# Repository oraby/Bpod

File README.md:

# Bpod

Kepecs Lab workspace, forked from Sanworks.

Used to modify Bpod code for use in Kepecs Lab.
General improvements will be contributed to Sanworks' repo.

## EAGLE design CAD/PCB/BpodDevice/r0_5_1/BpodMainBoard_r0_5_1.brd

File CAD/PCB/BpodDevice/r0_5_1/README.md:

# Bpod r0.5.1 PCB
Minor improvements compared to the original Bpod r0.5 release:
* Added bypass-capacitors to the VCC-inputs of all ICs
* Added GND polygon on top and bottom layer
* Rerouted the layout to reduce cross-talk between adjacent output ports

## Assembly instructions
Will be updted soon...  
For now see:  
https://sites.google.com/site/bpoddocumentation/assembling-bpod/instructions

## Bill of materials (BOM)
| Part Name | Description | Manufacturer | Name | Vendor | Part-Number |
| --- | --- | --- | --- | --- | --- |
| | Arduino Due | Arduino | Arduino Due | DigiKey | [1050-1049-ND](https://www.digikey.com/product-detail/en/arduino/A000062/1050-1049-ND "DigiKey 1050-1049-ND") |
| | DC/DC Converter | TDK Lambda | CC10-0512SF-E | DigiKey | [445-2433-ND](https://www.digikey.com/product-detail/en/CC10-0512SF-E/445-2433-ND "DigiKey 445-2433-ND") |
| `VALVE_REGISTER` | Power Shift Register | Texas Instruments | TPIC6A595 | DigiKey | [296-9007-5-ND](https://www.digikey.com/product-detail/en/texas-instruments/TPIC6A595NE/296-9007-5-ND "DigiKey 296-9007-5-ND") |
| `SYNC_REGISTER` | Shift Register | Texas Instruments, STMicro, NXP, … | 74HC595 | DigiKey | [296-1600-5-ND](https://www.digikey.com/product-detail/en/texas-instruments/SN74HC595N/296-1600-5-ND "DigiKey 296-1600-5-ND") |
| `5V_3V3_1/2/3` | 5V to 3.3V Converter (noninverting hex buffer) | Texas Instruments | CD4050BE | DigiKey | [296-2056-5-ND](https://www.digikey.com/product-detail/en/texas-instruments/CD4050BE/296-2056-5-ND "DigiKey 296-2056-5-ND") |
| `OPTOCOUPLER` | Opto-Coupler | Broadcom, Avago | HCPL-2231 | DigiKey | [516-1582-5-ND ](https://www.digikey.com/product-detail/en/broadcom-limited/HCPL-2231-000E/516-1582-5-ND "DigiKey 516-1582-5-ND ") |
| `Q3, Q4` | N-Channel MOSFET | ON Semi, STMicro, Microchip, NXP,… | 2N7000 | DigiKey | [2N7000FS-ND](https://www.digikey.com/product-detail/en/on-semiconductor/2N7000/2N7000FS-ND "DigiKey 2N7000FS-ND") |
| `LED` | RGB LED | Bivar Inc. | R50RGB-F-0160 | DigiKey | [492-1179-ND](https://www.digikey.com/product-detail/en/bivar-inc/R50RGB-F-0160/492-1179-ND "DigiKey 492-1179-ND") |
| `C1, C2, C3, C4, C5, C6` | 100 nF Bypass Capacitor (Ceramic) | Vishay, Kemet, AVX, … | 100 nF, 50 V, X7R | DigiKey | [BC5137-ND](https://www.digikey.com/product-detail/en/K104K10X7RF53L2/BC5137-ND "DigiKey BC5137-ND") |
| `R1` | 47 Ohm Current Limiting Common Cathode RGB LED | Stackpole, Yageo, Vishay, TE, … | 47 Ohm, 1/4 W, 1% | DigiKey | [BC4379CT-ND](https://www.digikey.com/product-detail/en/SFR2500004709FR500/BC4379CT-ND "DigiKey BC4379CT-ND") |
| `R2, R3` | 1 kOhm Current Limiting for Opto-Coupler | Stackpole, Yageo, Vishay, TE, … | 1 kOhm, 1/4 W, 1% | DigiKey | [RNF14FTD1K00CT-ND](https://www.digikey.com/product-detail/en/RNF14FTD1K00/RNF14FTD1K00CT-ND "DigiKey [RNF14FTD1K00CT-ND") |
| `R4, R5` | 10 kOhm Pull-Up BNC-Output | Stackpole, Yageo, Vishay, TE, … | 10 kOhm, 1/4 W, 1% | DigiKey | [RNF14FTD10K0CT-ND](https://www.digikey.com/product-detail/en/RNF14FTD10K0/RNF14FTD10K0CT-ND "DigiKey RNF14FTD10K0CT-ND") |
| | Socket DIP8 (OPTOCOUPLER) | On Shore, Assmann, TE, Amphenol, ... | DIP Socket 8 Pos | DigiKey | [ED3044-5-ND](https://www.digikey.com/product-detail/en/ED08DT/ED3044-5-ND "DigiKey ED3044-5-ND") |
| | Socket DIP16 (CD4050/74HC595) | On Shore, Assmann, TE, Amphenol, ... | DIP Socket 16 Pos | DigiKey | [ED3046-5-ND](https://www.digikey.com/product-detail/en/ED16DT/ED3046-5-ND "DigiKey ED3046-5-ND") |
| | Socket DIP20 (TPIC6A595) | On Shore, Assmann, TE, Amphenol, ... | DIP Socket 20 Pos | DigiKey | [ED3054-5-ND](https://www.digikey.com/product-detail/en/ED20DT/ED3054-5-ND "DigiKey ED3054-5-ND") |
| | Pinheader for Arduino Pins 0-21 & Analog (8-Pin) | Sparkfun | Stackable Header 8 Pin | Sparkfun | [PRT-09279](https://www.sparkfun.com/products/9279 "Sparkfun PRT-09279") |
| | Pinheader for Arduino Power Pins (6-Pin) | Sparkfun | Stackable Header 6 Pin | Sparkfun | [PRT-09280](https://www.sparkfun.com/products/9280 "Sparkfun PRT-09280") |
| | Pinheader for Arduino Pins 22-53 | Sullins, Amphenol, TE, … | Pinheader 36 Pos 0.1 spacing | DigiKey | [S2011EC-18-ND](https://www.digikey.com/product-detail/en/PRPC018DAAN-RC/S2011EC-18-ND "DigiKey S2011EC-18-ND") |
| | Header for Arduino ISP Pins| Sullins, Samtec, TE, … | Header (Female) 6 Pin | DigiKey | [S7106-ND](https://www.digikey.com/product-detail/en/sullins-connector-solutions/PPPC032LFBN-RC/S7106-ND "DigiKey S7106-ND") |
| `Ports` | RJ45 Ports | TE | Modular Jack 8P8C RJ45 | DigiKey | [A31442-ND](https://www.digikey.com/product-detail/en/5555164-1/A31442-ND "DigiKey A31442-ND") |
| `BNC` | BNC Ports | TE | BNC Jack 75 Ohm | DigiKey | [A97562-ND](https://www.digikey.com/product-detail/en/1-1634622-0/A97562-ND "DigiKey A97562-ND") |
| `Spring Terminal` | Spring Terminal for Wire I/Os | TE | Terminal Block 1-1986711-0 | DigiKey | [A104562-ND](https://www.digikey.com/product-detail/en/1-1986711-0/A104562-ND "DigiKey A104562-ND") |
| | Spacer for Arduino Due | Bivar Inc.  | Round Spacer Nylon 1/4" | DigiKey | [492-1074-ND](https://www.digikey.com/product-detail/en/9908-250/492-1074-ND "DigiKey 492-1074-ND") |
| | Spacer for Bpod PCB | Bivar Inc.  | Round Spacer Nylon 3/4" | DigiKey | [492-1081-ND](https://www.digikey.com/product-detail/en/9908-750/492-1081-ND "DigiKey 492-1081-ND") |
| | Screw for Arduino Due | B&F | Screw 4-40 Phillips, 0.625" thread length | DigiKey | [H348-ND](https://www.digikey.com/product-detail/en/b-f-fastener-supply/PMS-440-0063-PH/H348-ND "H348-ND") |
| | Screw for Bpod PCB | McMaster-Carr | Screw 4-40 Phillips, 1.125" thread length | McMaster-Carr | [91772A118](https://www.mcmaster.com/91772A118 "DigiKey 91772A118") |
| | Screws for Enclosure | B&F | Screw 4-40 Phillips, 0.5" thread length | DigiKey | [H346-ND](https://www.digikey.com/product-detail/en/b-f-fastener-supply/PMS-440-0050-PH/H346-ND "DigiKey H346-ND") |
| | Hex-Nuts| McMaster-Carr | Hex Nut 1/4" 4-40 | McMaster-Carr| [90480A005](https://www.mcmaster.com/90480A005 "DigiKey 90480A005") |

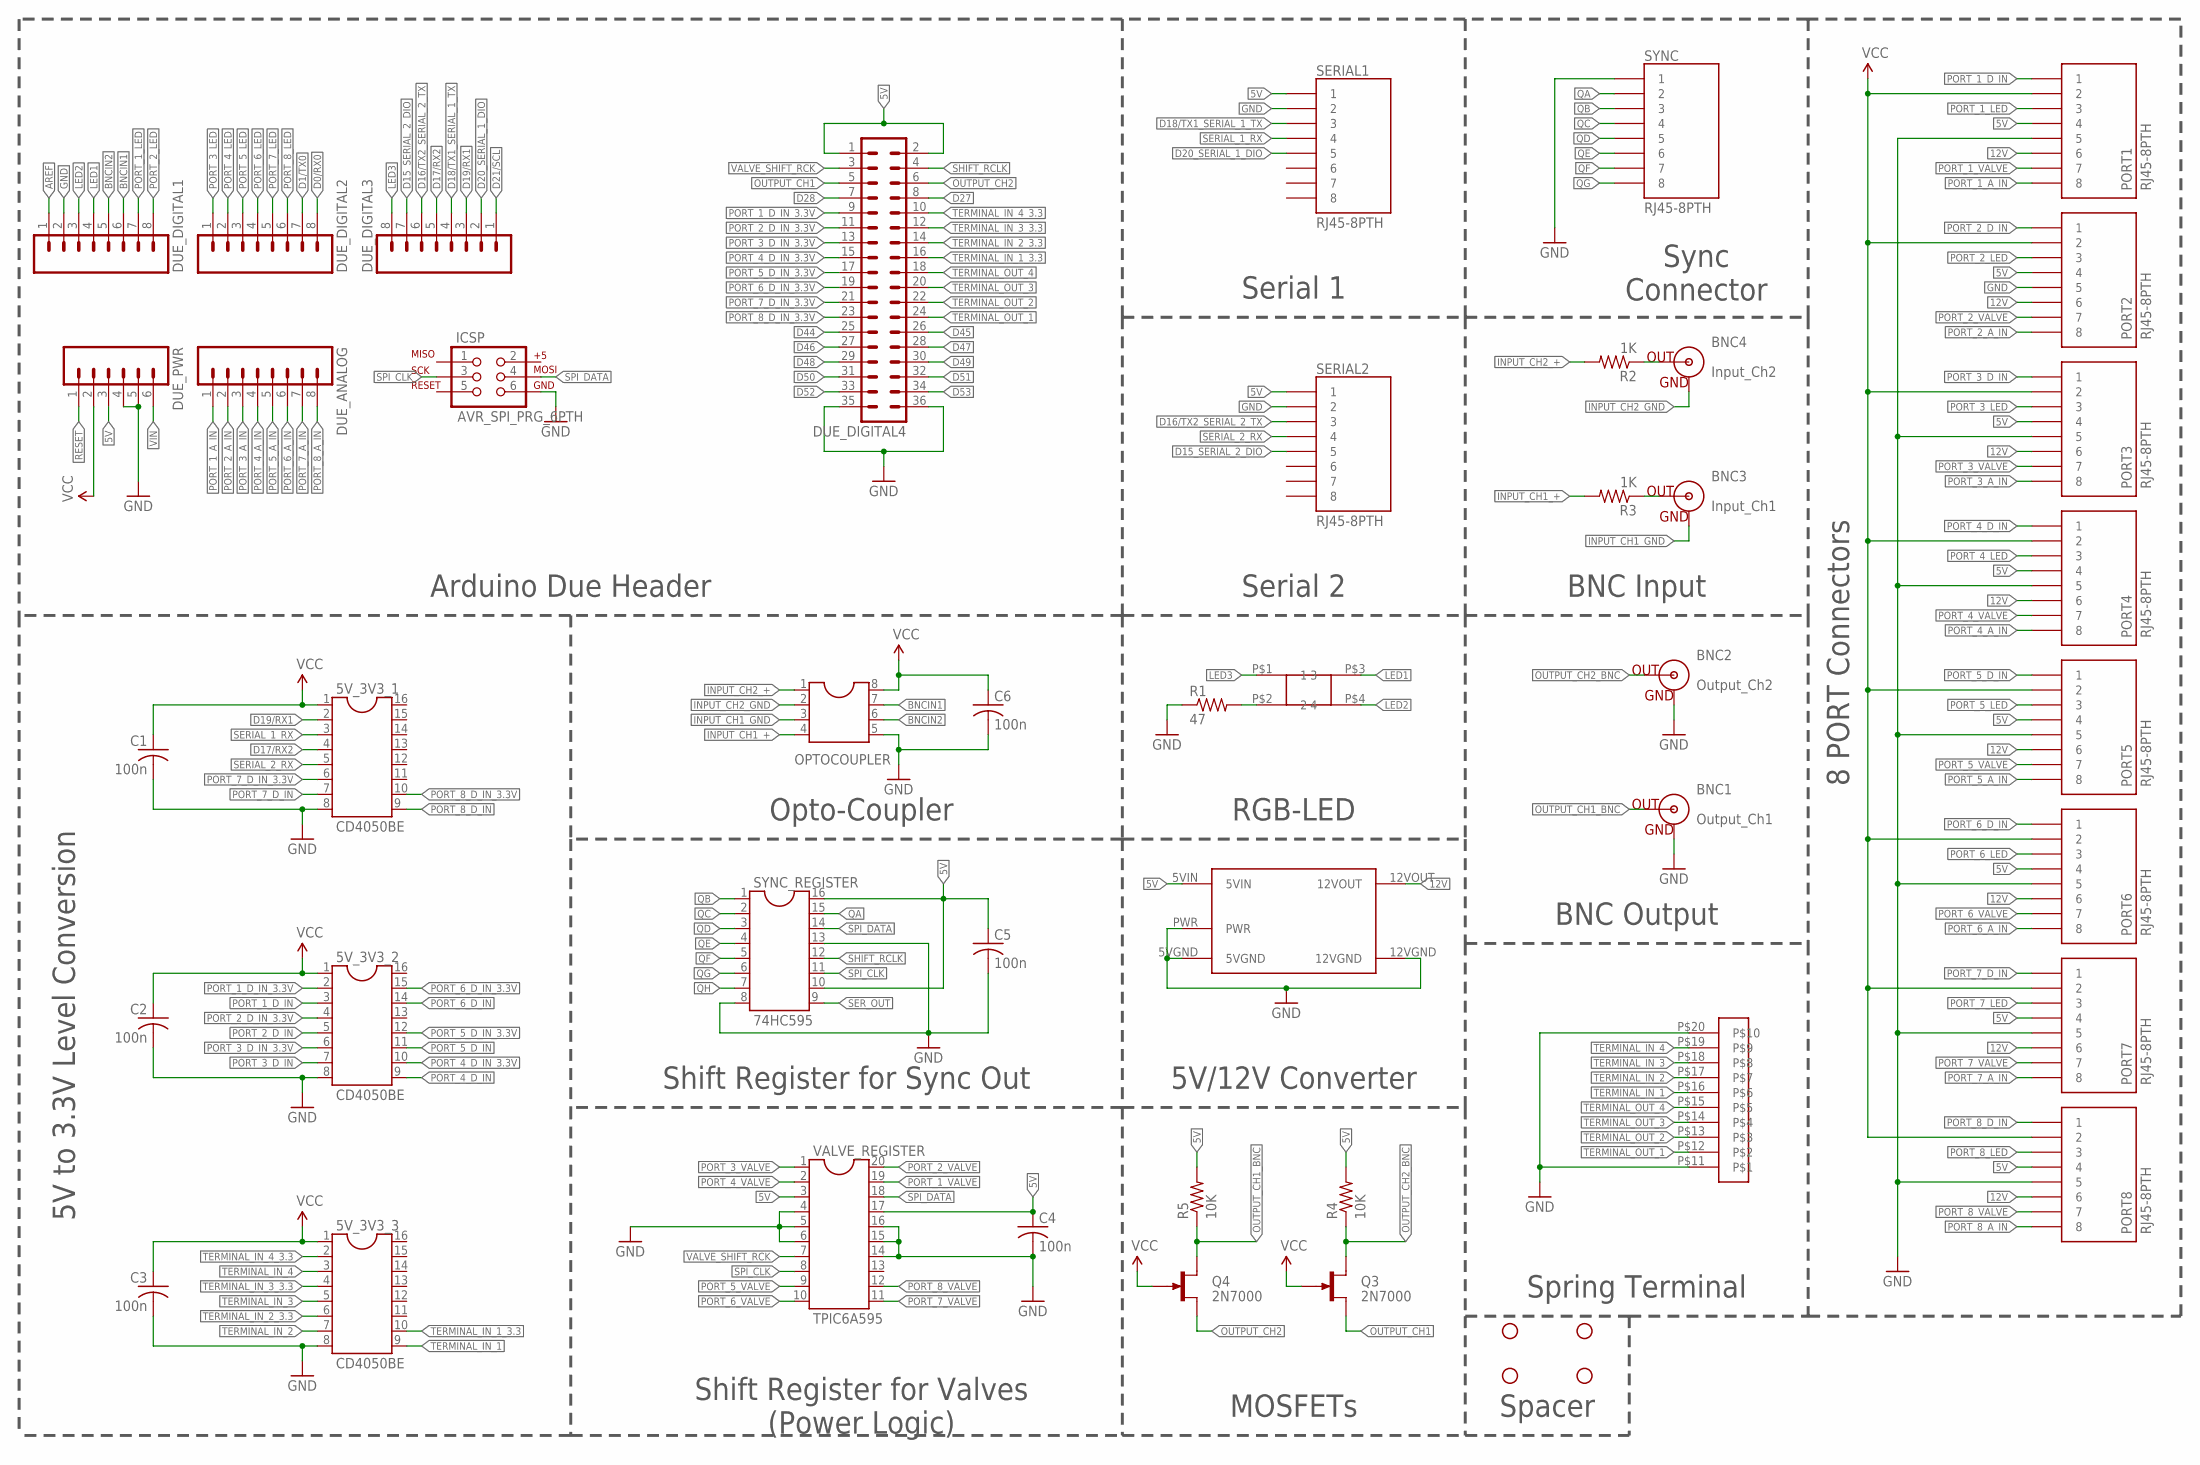
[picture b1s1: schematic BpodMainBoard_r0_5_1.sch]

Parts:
5V_3V3_1, 5V_3V3_2, 5V_3V3_3: CD4050BE; DIL16
BNC1: Output_Ch1; BNC
BNC2: Output_Ch2; BNC
BNC3: Input_Ch1; BNC
BNC4: Input_Ch2; BNC
C1, C2, C3, C4, C5, C6: 100n; C025-024X044
DUE_ANALOG: M081X08; 1X08
DUE_DIGITAL1, DUE_DIGITAL2, DUE_DIGITAL3: M081X08; 1X08
DUE_DIGITAL4: MA18-2
DUE_PWR: M06SIP; 1X06
ICSP: AVR_SPI_PRG_6PTH; 2X3
JP1, JP2, JP3, JP4: STAND-OFF
OPTOCOUPLER: DIL8; DIL08
PORT1, PORT2, PORT3, PORT4, PORT5, PORT6, PORT7, PORT8: RJ45-8PTH; RJ45-8
Q3, Q4: 2N7000; TO92F
R1: 47; 0207/10
R2, R3: 1K; 0207/10
R4, R5: 10K; 0207/10
SERIAL1, SERIAL2: RJ45-8PTH; RJ45-8
SPRINGTERMINAL: 10POS_SPRING_TERMINAL; 10POS_SCREW_TERMINAL
SYNC: RJ45-8PTH; RJ45-8
SYNC_REGISTER: 74HC595; DIL16
U$5: TDK_LAMBDA_5V_TO_12V; TDK_LAMBDA_5V_12V
U$8: SQUARE_TRICOLOR_LED
VALVE_REGISTER: TPIC6A595; DIL20

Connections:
5V: C4.1, C5.1, DUE_DIGITAL4.1, DUE_DIGITAL4.2, DUE_PWR.3, PORT1.4, PORT2.4, PORT3.4, PORT4.4, PORT5.4, PORT6.4, PORT7.4, PORT8.4, R4.2, R5.2, SERIAL1.1, SERIAL2.1, SYNC_REGISTER.10, SYNC_REGISTER.16, U$5.5VIN, VALVE_REGISTER.3, VALVE_REGISTER.17
12V: PORT1.6, PORT2.6, PORT3.6, PORT4.6, PORT5.6, PORT6.6, PORT7.6, PORT8.6, U$5.12VOUT
AREF: DUE_DIGITAL1.1
BNCIN1: DUE_DIGITAL1.6, OPTOCOUPLER.7
BNCIN2: DUE_DIGITAL1.5, OPTOCOUPLER.6
D0/RX0: DUE_DIGITAL2.8
D1/TX0: DUE_DIGITAL2.7
D15_SERIAL_2_DIO: DUE_DIGITAL3.7, SERIAL2.5
D16/TX2_SERIAL_2_TX: DUE_DIGITAL3.6, SERIAL2.3
D17/RX2: 5V_3V3_1.4, DUE_DIGITAL3.5
D18/TX1_SERIAL_1_TX: DUE_DIGITAL3.4, SERIAL1.3
D19/RX1: 5V_3V3_1.2, DUE_DIGITAL3.3
D20_SERIAL_1_DIO: DUE_DIGITAL3.2, SERIAL1.5
D21/SCL: DUE_DIGITAL3.1
D27: DUE_DIGITAL4.8
D28: DUE_DIGITAL4.7
D44: DUE_DIGITAL4.25
D45: DUE_DIGITAL4.26
D46: DUE_DIGITAL4.27
D47: DUE_DIGITAL4.28
D48: DUE_DIGITAL4.29
D49: DUE_DIGITAL4.30
D50: DUE_DIGITAL4.31
D51: DUE_DIGITAL4.32
D52: DUE_DIGITAL4.33
D53: DUE_DIGITAL4.34
GND: 5V_3V3_1.8, 5V_3V3_2.8, 5V_3V3_3.8, BNC1.GND, BNC2.GND, C1.2, C2.2, C3.2, C4.2, C5.2, C6.2, DUE_DIGITAL1.2, DUE_DIGITAL4.35, DUE_DIGITAL4.36, DUE_PWR.4, DUE_PWR.5, ICSP.6, OPTOCOUPLER.5, PORT1.5, PORT2.5, PORT3.5, PORT4.5, PORT5.5, PORT6.5, PORT7.5, PORT8.5, R1.1, SERIAL1.2, SERIAL2.2, SPRINGTERMINAL.P$11, SPRINGTERMINAL.P$20, SYNC.1, SYNC_REGISTER.8, SYNC_REGISTER.13, U$5.5VGND, U$5.12VGND, U$5.PWR, VALVE_REGISTER.4, VALVE_REGISTER.5, VALVE_REGISTER.6, VALVE_REGISTER.14, VALVE_REGISTER.15, VALVE_REGISTER.16
INPUT_CH1_+: OPTOCOUPLER.4, R3.2
INPUT_CH1_GND: BNC3.GND, OPTOCOUPLER.3
INPUT_CH2_+: OPTOCOUPLER.1, R2.2
INPUT_CH2_GND: BNC4.GND, OPTOCOUPLER.2
INPUT_CH_1: BNC3.S (OUT), R3.1
INPUT_CH_2: BNC4.S (OUT), R2.1
LED1: DUE_DIGITAL1.4, U$8.P$3 (3)
LED2: DUE_DIGITAL1.3, U$8.P$4 (4)
LED3: DUE_DIGITAL3.8, U$8.P$1 (1)
LED_GND: R1.2, U$8.P$2 (2)
OUTPUT_CH1: DUE_DIGITAL4.5, Q3.S
OUTPUT_CH1_BNC: BNC1.S (OUT), Q4.D, R5.1
OUTPUT_CH2: DUE_DIGITAL4.6, Q4.S
OUTPUT_CH2_BNC: BNC2.S (OUT), Q3.D, R4.1
PORT_1_A_IN: DUE_ANALOG.1, PORT1.8
PORT_1_D_IN: 5V_3V3_2.3, PORT1.1
PORT_1_D_IN_3.3V: 5V_3V3_2.2, DUE_DIGITAL4.9
PORT_1_LED: DUE_DIGITAL1.7, PORT1.3
PORT_1_VALVE: PORT1.7, VALVE_REGISTER.19
PORT_2_A_IN: DUE_ANALOG.2, PORT2.8
PORT_2_D_IN: 5V_3V3_2.5, PORT2.1
PORT_2_D_IN_3.3V: 5V_3V3_2.4, DUE_DIGITAL4.11
PORT_2_LED: DUE_DIGITAL1.8, PORT2.3
PORT_2_VALVE: PORT2.7, VALVE_REGISTER.20
PORT_3_A_IN: DUE_ANALOG.3, PORT3.8
PORT_3_D_IN: 5V_3V3_2.7, PORT3.1
PORT_3_D_IN_3.3V: 5V_3V3_2.6, DUE_DIGITAL4.13
PORT_3_LED: DUE_DIGITAL2.1, PORT3.3
PORT_3_VALVE: PORT3.7, VALVE_REGISTER.1
PORT_4_A_IN: DUE_ANALOG.4, PORT4.8
PORT_4_D_IN: 5V_3V3_2.9, PORT4.1
PORT_4_D_IN_3.3V: 5V_3V3_2.10, DUE_DIGITAL4.15
PORT_4_LED: DUE_DIGITAL2.2, PORT4.3
PORT_4_VALVE: PORT4.7, VALVE_REGISTER.2
PORT_5_A_IN: DUE_ANALOG.5, PORT5.8
PORT_5_D_IN: 5V_3V3_2.11, PORT5.1
PORT_5_D_IN_3.3V: 5V_3V3_2.12, DUE_DIGITAL4.17
PORT_5_LED: DUE_DIGITAL2.3, PORT5.3
PORT_5_VALVE: PORT5.7, VALVE_REGISTER.9
PORT_6_A_IN: DUE_ANALOG.6, PORT6.8
PORT_6_D_IN: 5V_3V3_2.14, PORT6.1
PORT_6_D_IN_3.3V: 5V_3V3_2.15, DUE_DIGITAL4.19
PORT_6_LED: DUE_DIGITAL2.4, PORT6.3
PORT_6_VALVE: PORT6.7, VALVE_REGISTER.10
PORT_7_A_IN: DUE_ANALOG.7, PORT7.8
PORT_7_D_IN: 5V_3V3_1.7, PORT7.1
PORT_7_D_IN_3.3V: 5V_3V3_1.6, DUE_DIGITAL4.21
PORT_7_LED: DUE_DIGITAL2.5, PORT7.3
PORT_7_VALVE: PORT7.7, VALVE_REGISTER.11
PORT_8_A_IN: DUE_ANALOG.8, PORT8.8
PORT_8_D_IN: 5V_3V3_1.9, PORT8.1
PORT_8_D_IN_3.3V: 5V_3V3_1.10, DUE_DIGITAL4.23
PORT_8_LED: DUE_DIGITAL2.6, PORT8.3
PORT_8_VALVE: PORT8.7, VALVE_REGISTER.12
QA: SYNC.2, SYNC_REGISTER.15
QB: SYNC.3, SYNC_REGISTER.1
QC: SYNC.4, SYNC_REGISTER.2
QD: SYNC.5, SYNC_REGISTER.3
QE: SYNC.6, SYNC_REGISTER.4
QF: SYNC.7, SYNC_REGISTER.5
QG: SYNC.8, SYNC_REGISTER.6
QH: SYNC_REGISTER.7
RESET: DUE_PWR.1
SERIAL_1_RX: 5V_3V3_1.3, SERIAL1.4
SERIAL_2_RX: 5V_3V3_1.5, SERIAL2.4
SER_OUT: SYNC_REGISTER.9
SHIFT_RCLK: DUE_DIGITAL4.4, SYNC_REGISTER.12
SPI_CLK: ICSP.3, SYNC_REGISTER.11, VALVE_REGISTER.8
SPI_DATA: ICSP.4, SYNC_REGISTER.14, VALVE_REGISTER.18
TERMINAL_IN_1: 5V_3V3_3.9, SPRINGTERMINAL.P$16
TERMINAL_IN_1_3.3: 5V_3V3_3.10, DUE_DIGITAL4.16
TERMINAL_IN_2: 5V_3V3_3.7, SPRINGTERMINAL.P$17
TERMINAL_IN_2_3.3: 5V_3V3_3.6, DUE_DIGITAL4.14
TERMINAL_IN_3: 5V_3V3_3.5, SPRINGTERMINAL.P$18
TERMINAL_IN_3_3.3: 5V_3V3_3.4, DUE_DIGITAL4.12
TERMINAL_IN_4: 5V_3V3_3.3, SPRINGTERMINAL.P$19
TERMINAL_IN_4_3.3: 5V_3V3_3.2, DUE_DIGITAL4.10
TERMINAL_OUT_1: DUE_DIGITAL4.24, SPRINGTERMINAL.P$12
TERMINAL_OUT_2: DUE_DIGITAL4.22, SPRINGTERMINAL.P$13
TERMINAL_OUT_3: DUE_DIGITAL4.20, SPRINGTERMINAL.P$14
TERMINAL_OUT_4: DUE_DIGITAL4.18, SPRINGTERMINAL.P$15
VALVE_SHIFT_RCK: DUE_DIGITAL4.3, VALVE_REGISTER.7
VCC: 5V_3V3_1.1, 5V_3V3_2.1, 5V_3V3_3.1, C1.1, C2.1, C3.1, C6.1, DUE_PWR.2, OPTOCOUPLER.8, PORT1.2, PORT2.2, PORT3.2, PORT4.2, PORT5.2, PORT6.2, PORT7.2, PORT8.2, Q3.G, Q4.G
VIN: DUE_PWR.6

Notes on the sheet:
8 PORT Connectors
Sync Connector
BNC Input
BNC Output
Spring Terminal
Serial 1
Serial 2
Spacer
Arduino Due Header
5V to 3.3V Level Conversion
Shift Register for Valves (Power Logic)
RGB-LED
Opto-Coupler
Shift Register for Sync Out
5V/12V Converter
MOSFETs

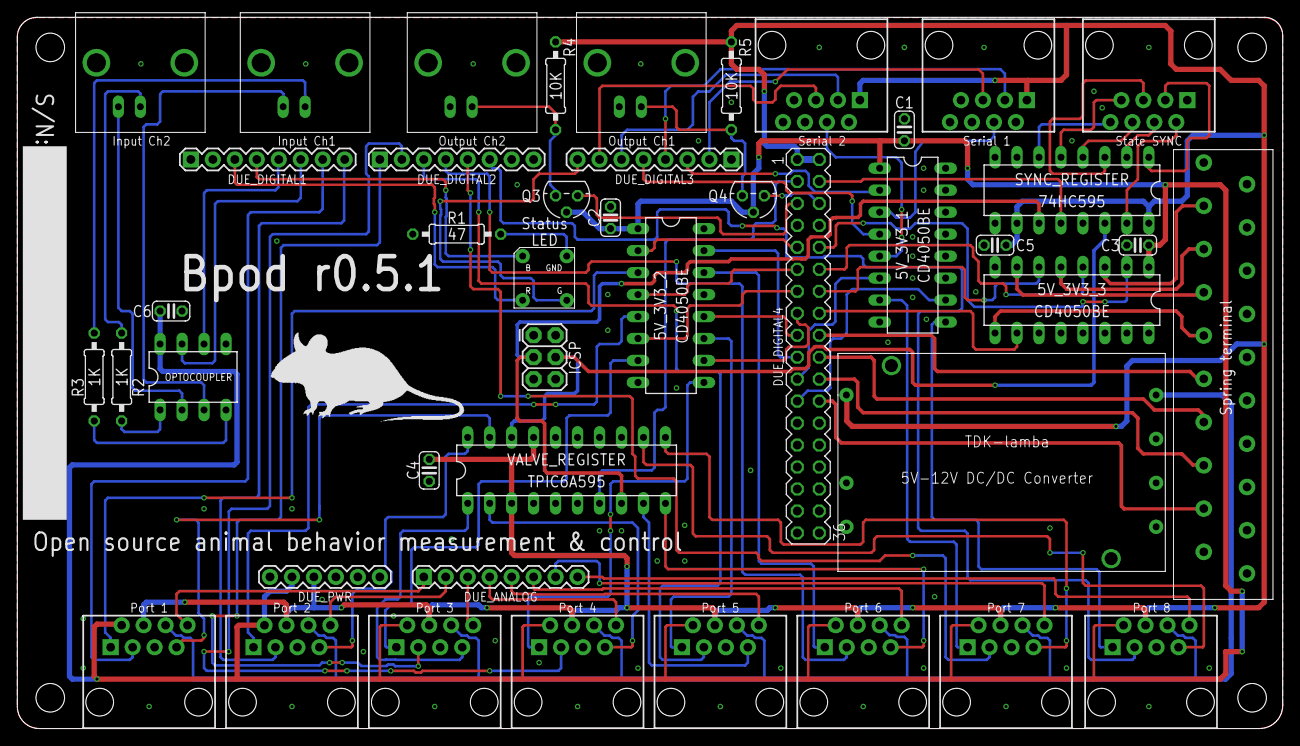
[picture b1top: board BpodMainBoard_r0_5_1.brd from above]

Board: 2 copper layers, 146.3 x 82.2 mm, 49 parts (0 on the bottom side), 91 nets.

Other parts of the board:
U$7: MOUSELOGO

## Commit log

2016-06-29 Added to .gitignore folders Calibration Files, Data, and Protocols
2016-06-29 Added file .gitmodules to .gitignore.
2016-06-30 Added uicontrol styles 'togglebutton' and 'pushbutton' to GUI
2016-07-01 Work in progress
2016-07-05 Tabs working. Now adding uitable.
2016-07-05 Accepts meta.style uitables. Stores handles in Matlab 2016.
2016-07-15 Added purpose of Kepecs Bpod fork
2016-08-04 Bpod Settings, Calibration Files, and Protocols are saved in the user-specific home directory (e.g. /Users/JoeUser/BpodUser/). This BpodUser directory is created automatically if not found. BpodInput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
2016-08-05 checks for calibration and settings folders in BpodUserPath first and copies whole folder, if they don't exist. removes unecessary logical cses.
2016-08-08 In progress, still need to finish updating instances of BpodPath
2016-08-09 Removes reference to undefined variable S. Moves redundant bits of code out of if clause.
2016-08-09 in progress: dialog prompts user to create BpodUser if not detected
2016-08-09 Fixes bug with unspecified tabs
2016-08-15 [in progress] Added browse button for browsing of BpodUser directory. Nothing happens after that.
2016-09-06 Updated LaunchManager, RunProtocol, BpodLiquidCalibration, and Pipeline to utilize BpodSystem.BpodUserPath where appropriate. Still need to test these changes on a rig.
2016-09-06 adds mat file containing string to BpodUserPath in Bpod home directory. uses string for BpodUserPath. default is home directory.
2016-09-07 changed mat file to txt file
2016-09-16 Added menu bar to Parameter GUI allowing to save current TaskParameters to current settings file (save) or to new settings file (save as).
2016-09-16 prevents protocol from crashing when you hit "cancel" while saving.
2016-09-16 Solves sync-issue by adding a 'get' option to BpodParameterGUI. Shows current settings, subject, protocol.
2016-09-19 more consistent appearance of menus
2016-09-21 corrected save menu callback function.
2016-09-22 corrects error in 'get'.
2016-09-23 Replaced with latest port breakout board design from Sanworks (LED adjust, not IR adjust)
2016-09-28 When stopping a Bpod protocol the custom user script UserKillScript.m located in the current protocol folder is executed, if it exists. Allows for custom actions at session end (eg email figures, etc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
2016-10-13 Ignore customUserPath text file
2016-10-13 Made SaveBpodProtocolSettings compatible with more recent versions of matlab (in which you can't save a structure field directly using "save")
2016-10-24 Custom location for BpodUser (#8)
    Adds .txt file containing string to BpodUserPath in Bpod home directory. Default is home directory.
2016-11-03 Very minor: 1) ignore BpodUserPath.txt 2) fix SaveBpodProtocolSettings so it works with more recent matlab versions. I've tested these changes. Sorry for not doing a pull request!!!
2017-03-30 added edit text/string option to parameter GUI
2017-04-08 testing changes to deal with TrialTypes intialized as vector of NaNs
2017-05-16 As the olfactometer IP address is often a string, turning it into a string makes an error
2017-05-18 As the olfactometer IP address is often a string, turning it into a string makes an error. I added a line to test wheter it is a number or not.
2017-05-18 As the olfactometer IP address is often a string, turning it into a string makes an error - debug
2017-08-08 script to change bpod user before intializing bpod
2017-09-21 Haven't worked on it for a while. No idea what this is.
2018-02-08 Debug GUI table to be editable for all columns.
2018-02-09 Branch for people to test setBpodDefaultSettings function- allows you to add new settings parameters to your protocol and to recycle your old, saved protocol settings but updated to reflect the intro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
2018-02-09 bit better doc
2018-04-07 Version of TrialTypeOutcome Plot that handles having trial types and outcomes built on the fly starting from an empty array Also added *.asv to gitignore
2018-04-09 testing 'popupmenutext' : returns selected string rather than its numeric index
2018-04-10 Succesfully tested popupmenutext GUI style, like popupmenu but returns string from menu list rather than its numeric index
2018-05-08 adding computer-specific settings files to .gitignore
2018-05-08 Added Sensors path to users
2018-05-14 ParameterGUI: Arrange switch cases sequentially
2018-05-14 ParameterGUI: Add support for slider component
2018-05-24 GUI: Add support for callback
2018-06-15 Revised the r0.5 board layout to reduce the possibility for cross-talks between different ports and added the necessary but missing bypass capacitors (100 nF) to every IC (should also increase stabil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
2018-12-03 Corrected the printings on the PCB for BNC I/Os and Serial ports (numbers were mixed up) and added BOM
2019-11-06 Added changes to make the current implementation compatible with the ASUS Xonar SE 5.1 soundcard
2019-11-08 Revised data acquisition towards session based interface and extended and refactored the calibrator's GUI completely. Futhermore, updated deprecated code for PSD estimation and introduced additional 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
2019-11-16 Added functionality to calibrate two speakers simultaneously (joined) and extended the speaker testing plugin as well as the function to generate a calibrated tone.
2019-11-22 Added functionality into the SoundCalibration Plugin to calibrate the sound output using audio files.
2020-02-19 BpodParameterGUI: Handle style in a separate function
    This improves code readability and makes the code more modular and
    reusable. This change will is also needed for a future change.
2020-02-19 GUI: Support more meta parameters for tables
    The changes attempts to map directly the meta parameters to MATLAB's
    uItable formatting parameters.
2020-02-19 Refactor length of panels to fit more fields in a GUI column
2020-02-19 Format: Remove some EOL trailing spaces
2020-02-19 Use '~isEqual' instead of '~=' to compare values
2020-02-19 GUI: Fix value re-appearing multiple times causing others not to sync
2020-02-19 GUI: Fix bug where string was not declared
2020-02-19 Change GUI panels drawing spaces parameters
    These values look to be more accurate without extra white spaces.
